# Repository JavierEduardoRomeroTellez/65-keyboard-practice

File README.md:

## 65-keyboard-practice
 Triying to make a 65% keyboard

#Images

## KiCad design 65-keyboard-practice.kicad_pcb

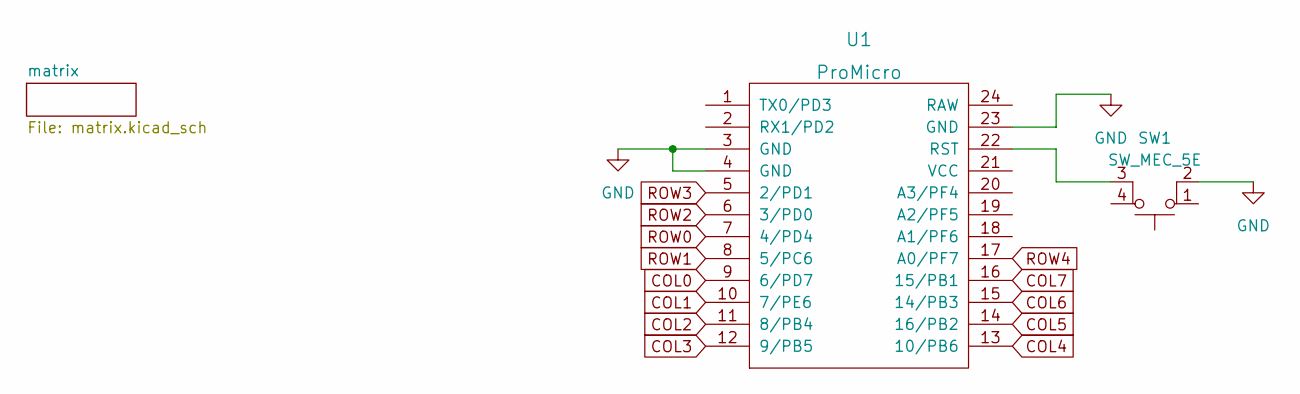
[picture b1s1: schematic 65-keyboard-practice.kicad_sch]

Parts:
SW1: SW_MEC_5E; PushButton_6x6mm_TH
U1: ProMicro; ArduinoProMicro

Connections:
COL0: U1.9 (6/PD7); also elsewhere on the board
COL1: U1.10 (7/PE6); also elsewhere on the board
COL2: U1.11 (8/PB4); also elsewhere on the board
COL3: U1.12 (9/PB5); also elsewhere on the board
COL4: U1.13 (10/PB6); also elsewhere on the board
COL5: U1.14 (16/PB2); also elsewhere on the board
COL6: U1.15 (14/PB3); also elsewhere on the board
COL7: U1.16 (15/PB1); also elsewhere on the board
GND: SW1.2, U1.3 (GND), U1.4 (GND), U1.23 (GND)
unnamed: SW1.3 (K), U1.22 (RST)
ROW0: U1.7 (4/PD4); also elsewhere on the board
ROW1: U1.8 (5/PC6); also elsewhere on the board
ROW2: U1.6 (3/PD0); also elsewhere on the board
ROW3: U1.5 (2/PD1); also elsewhere on the board
ROW4: U1.17 (A0/PF7); also elsewhere on the board

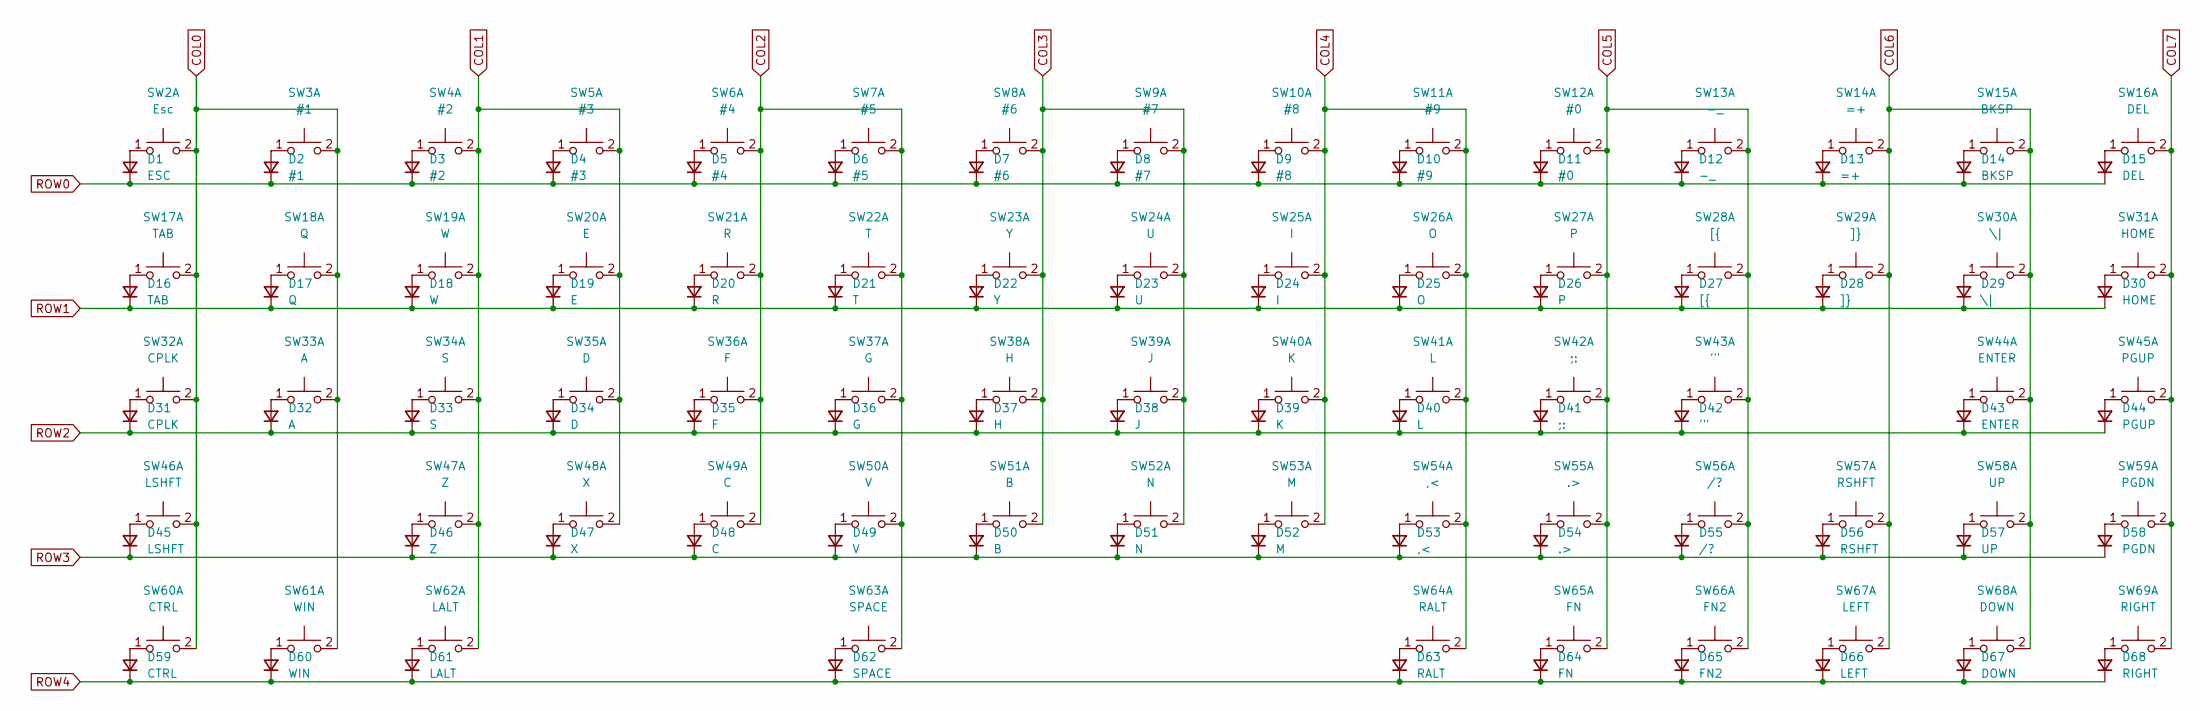
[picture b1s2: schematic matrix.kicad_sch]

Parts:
D1: ESC; D_DO-35_SOD27_P5.08mm_Horizontal
D2: #1; D_DO-35_SOD27_P5.08mm_Horizontal
D3: #2; D_DO-35_SOD27_P5.08mm_Horizontal
D4: #3; D_DO-35_SOD27_P5.08mm_Horizontal
D5: #4; D_DO-35_SOD27_P5.08mm_Horizontal
D6: #5; D_DO-35_SOD27_P5.08mm_Horizontal
D7: #6; D_DO-35_SOD27_P5.08mm_Horizontal
D8: #7; D_DO-35_SOD27_P5.08mm_Horizontal
D9: #8; D_DO-35_SOD27_P5.08mm_Horizontal
D10: #9; D_DO-35_SOD27_P5.08mm_Horizontal
D11: #0; D_DO-35_SOD27_P5.08mm_Horizontal
D12: -_; D_DO-35_SOD27_P5.08mm_Horizontal
D13: =+; D_DO-35_SOD27_P5.08mm_Horizontal
D14: BKSP; D_DO-35_SOD27_P5.08mm_Horizontal
D15: DEL; D_DO-35_SOD27_P5.08mm_Horizontal
D16: TAB; D_DO-35_SOD27_P5.08mm_Horizontal
D17: Q; D_DO-35_SOD27_P5.08mm_Horizontal
D18: W; D_DO-35_SOD27_P5.08mm_Horizontal
D19: E; D_DO-35_SOD27_P5.08mm_Horizontal
D20: R; D_DO-35_SOD27_P5.08mm_Horizontal
D21: T; D_DO-35_SOD27_P5.08mm_Horizontal
D22: Y; D_DO-35_SOD27_P5.08mm_Horizontal
D23: U; D_DO-35_SOD27_P5.08mm_Horizontal
D24: I; D_DO-35_SOD27_P5.08mm_Horizontal
D25: O; D_DO-35_SOD27_P5.08mm_Horizontal
D26: P; D_DO-35_SOD27_P5.08mm_Horizontal
D27: [{; D_DO-35_SOD27_P5.08mm_Horizontal
D28: ]}; D_DO-35_SOD27_P5.08mm_Horizontal
D29: \|; D_DO-35_SOD27_P5.08mm_Horizontal
D30: HOME; D_DO-35_SOD27_P5.08mm_Horizontal
D31: CPLK; D_DO-35_SOD27_P5.08mm_Horizontal
D32: A; D_DO-35_SOD27_P5.08mm_Horizontal
D33: S; D_DO-35_SOD27_P5.08mm_Horizontal
D34: D; D_DO-35_SOD27_P5.08mm_Horizontal
D35: F; D_DO-35_SOD27_P5.08mm_Horizontal
D36: G; D_DO-35_SOD27_P5.08mm_Horizontal
D37: H; D_DO-35_SOD27_P5.08mm_Horizontal
D38: J; D_DO-35_SOD27_P5.08mm_Horizontal
D39: K; D_DO-35_SOD27_P5.08mm_Horizontal
D40: L; D_DO-35_SOD27_P5.08mm_Horizontal
D41: ;:; D_DO-35_SOD27_P5.08mm_Horizontal
D42: '"; D_DO-35_SOD27_P5.08mm_Horizontal
D43: ENTER; D_DO-35_SOD27_P5.08mm_Horizontal
D44: PGUP; D_DO-35_SOD27_P5.08mm_Horizontal
D45: LSHFT; D_DO-35_SOD27_P5.08mm_Horizontal
D46: Z; D_DO-35_SOD27_P5.08mm_Horizontal
D47: X; D_DO-35_SOD27_P5.08mm_Horizontal
D48: C; D_DO-35_SOD27_P5.08mm_Horizontal
D49: V; D_DO-35_SOD27_P5.08mm_Horizontal
D50: B; D_DO-35_SOD27_P5.08mm_Horizontal
D51: N; D_DO-35_SOD27_P5.08mm_Horizontal
D52: M; D_DO-35_SOD27_P5.08mm_Horizontal
D53: ,<; D_DO-35_SOD27_P5.08mm_Horizontal
D54: .>; D_DO-35_SOD27_P5.08mm_Horizontal
D55: /?; D_DO-35_SOD27_P5.08mm_Horizontal
D56: RSHFT; D_DO-35_SOD27_P5.08mm_Horizontal
D57: UP; D_DO-35_SOD27_P5.08mm_Horizontal
D58: PGDN; D_DO-35_SOD27_P5.08mm_Horizontal
D59: CTRL; D_DO-35_SOD27_P5.08mm_Horizontal
D60: WIN; D_DO-35_SOD27_P5.08mm_Horizontal
D61: LALT; D_DO-35_SOD27_P5.08mm_Horizontal
D62: SPACE; D_DO-35_SOD27_P5.08mm_Horizontal
D63: RALT; D_DO-35_SOD27_P5.08mm_Horizontal
D64: FN; D_DO-35_SOD27_P5.08mm_Horizontal
D65: FN2; D_DO-35_SOD27_P5.08mm_Horizontal
D66: LEFT; D_DO-35_SOD27_P5.08mm_Horizontal
D67: DOWN; D_DO-35_SOD27_P5.08mm_Horizontal
D68: RIGHT; D_DO-35_SOD27_P5.08mm_Horizontal
SW2: Esc; MXOnly-1U-Hotswap
SW3: #1; MXOnly-1U-Hotswap
SW4: #2; MXOnly-1U-Hotswap
SW5: #3; MXOnly-1U-Hotswap
SW6: #4; MXOnly-1U-Hotswap
SW7: #5; MXOnly-1U-Hotswap
SW8: #6; MXOnly-1U-Hotswap
SW9: #7; MXOnly-1U-Hotswap
SW10: #8; MXOnly-1U-Hotswap
SW11: #9; MXOnly-1U-Hotswap
SW12: #0; MXOnly-1U-Hotswap
SW13: -_; MXOnly-1U-Hotswap
SW14: =+; MXOnly-1U-Hotswap
SW15: BKSP; MXOnly-2U-Hotswap
SW16: DEL; MXOnly-1U-Hotswap
SW17: TAB; MXOnly-1.5U-Hotswap
SW18: Q; MXOnly-1U-Hotswap
SW19: W; MXOnly-1U-Hotswap
SW20: E; MXOnly-1U-Hotswap
SW21: R; MXOnly-1U-Hotswap
SW22: T; MXOnly-1U-Hotswap
SW23: Y; MXOnly-1U-Hotswap
SW24: U; MXOnly-1U-Hotswap
SW25: I; MXOnly-1U-Hotswap
SW26: O; MXOnly-1U-Hotswap
SW27: P; MXOnly-1U-Hotswap
SW28: [{; MXOnly-1U-Hotswap
SW29: ]}; MXOnly-1U-Hotswap
SW30: \|; MXOnly-1.5U-Hotswap
SW31: HOME; MXOnly-1U-Hotswap
SW32: CPLK; MXOnly-1.75U-Hotswap
SW33: A; MXOnly-1U-Hotswap
SW34: S; MXOnly-1U-Hotswap
SW35: D; MXOnly-1U-Hotswap
SW36: F; MXOnly-1U-Hotswap
SW37: G; MXOnly-1U-Hotswap
SW38: H; MXOnly-1U-Hotswap
SW39: J; MXOnly-1U-Hotswap
SW40: K; MXOnly-1U-Hotswap
SW41: L; MXOnly-1U-Hotswap
SW42: ;:; MXOnly-1U-Hotswap
SW43: '"; MXOnly-1U-Hotswap
SW44: ENTER; MXOnly-2.25U-Hotswap
SW45: PGUP; MXOnly-1U-Hotswap
SW46: LSHFT; MXOnly-2.25U-Hotswap
SW47: Z; MXOnly-1U-Hotswap
SW48: X; MXOnly-1U-Hotswap
SW49: C; MXOnly-1U-Hotswap
SW50: V; MXOnly-1U-Hotswap
SW51: B; MXOnly-1U-Hotswap
SW52: N; MXOnly-1U-Hotswap
SW53: M; MXOnly-1U-Hotswap
SW54: ,<; MXOnly-1U-Hotswap
SW55: .>; MXOnly-1U-Hotswap
SW56: /?; MXOnly-1U-Hotswap
SW57: RSHFT; MXOnly-1.75U-Hotswap
SW58: UP; MXOnly-1U-Hotswap
SW59: PGDN; MXOnly-1U-Hotswap
SW60: CTRL; MXOnly-1.5U-Hotswap
SW61: WIN; MXOnly-1.25U-Hotswap
SW62: LALT; MXOnly-1.25U-Hotswap
SW63: SPACE; MXOnly-6U-Centered-Hotswap
SW64: RALT; MXOnly-1U-Hotswap
SW65: FN; MXOnly-1U-Hotswap
SW66: FN2; MXOnly-1U-Hotswap
SW67: LEFT; MXOnly-1U-Hotswap
SW68: DOWN; MXOnly-1U-Hotswap
SW69: RIGHT; MXOnly-1U-Hotswap

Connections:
COL0: SW2.2, SW3.2, SW17.2, SW18.2, SW32.2, SW33.2, SW46.2, SW60.2, SW61.2; also elsewhere on the board
COL1: SW4.2, SW5.2, SW19.2, SW20.2, SW34.2, SW35.2, SW47.2, SW48.2, SW62.2; also elsewhere on the board
COL2: SW6.2, SW7.2, SW21.2, SW22.2, SW36.2, SW37.2, SW49.2, SW50.2, SW63.2; also elsewhere on the board
COL3: SW8.2, SW9.2, SW23.2, SW24.2, SW38.2, SW39.2, SW51.2, SW52.2; also elsewhere on the board
COL4: SW10.2, SW11.2, SW25.2, SW26.2, SW40.2, SW41.2, SW53.2, SW54.2, SW64.2; also elsewhere on the board
COL5: SW12.2, SW13.2, SW27.2, SW28.2, SW42.2, SW43.2, SW55.2, SW56.2, SW65.2, SW66.2; also elsewhere on the board
COL6: SW14.2, SW15.2, SW29.2, SW30.2, SW44.2, SW57.2, SW58.2, SW67.2, SW68.2; also elsewhere on the board
COL7: SW16.2, SW31.2, SW45.2, SW59.2, SW69.2; also elsewhere on the board
unnamed: D1.2 (A), SW2.1
unnamed: D2.2 (A), SW3.1
unnamed: D3.2 (A), SW4.1
unnamed: D4.2 (A), SW5.1
unnamed: D5.2 (A), SW6.1
unnamed: D6.2 (A), SW7.1
unnamed: D7.2 (A), SW8.1
unnamed: D8.2 (A), SW9.1
unnamed: D9.2 (A), SW10.1
unnamed: D10.2 (A), SW11.1
unnamed: D11.2 (A), SW12.1
unnamed: D12.2 (A), SW13.1
unnamed: D13.2 (A), SW14.1
unnamed: D14.2 (A), SW15.1
unnamed: D15.2 (A), SW16.1
unnamed: D16.2 (A), SW17.1
unnamed: D17.2 (A), SW18.1
unnamed: D18.2 (A), SW19.1
unnamed: D19.2 (A), SW20.1
unnamed: D20.2 (A), SW21.1
unnamed: D21.2 (A), SW22.1
unnamed: D22.2 (A), SW23.1
unnamed: D23.2 (A), SW24.1
unnamed: D24.2 (A), SW25.1
unnamed: D25.2 (A), SW26.1
unnamed: D26.2 (A), SW27.1
unnamed: D27.2 (A), SW28.1
unnamed: D28.2 (A), SW29.1
unnamed: D29.2 (A), SW30.1
unnamed: D30.2 (A), SW31.1
unnamed: D31.2 (A), SW32.1
unnamed: D32.2 (A), SW33.1
unnamed: D33.2 (A), SW34.1
unnamed: D34.2 (A), SW35.1
unnamed: D35.2 (A), SW36.1
unnamed: D36.2 (A), SW37.1
unnamed: D37.2 (A), SW38.1
unnamed: D38.2 (A), SW39.1
unnamed: D39.2 (A), SW40.1
unnamed: D40.2 (A), SW41.1
unnamed: D41.2 (A), SW42.1
unnamed: D42.2 (A), SW43.1
unnamed: D43.2 (A), SW44.1
unnamed: D44.2 (A), SW45.1
unnamed: D45.2 (A), SW46.1
unnamed: D46.2 (A), SW47.1
unnamed: D47.2 (A), SW48.1
unnamed: D48.2 (A), SW49.1
unnamed: D49.2 (A), SW50.1
unnamed: D50.2 (A), SW51.1
unnamed: D51.2 (A), SW52.1
unnamed: D52.2 (A), SW53.1
unnamed: D53.2 (A), SW54.1
unnamed: D54.2 (A), SW55.1
unnamed: D55.2 (A), SW56.1
unnamed: D56.2 (A), SW57.1
unnamed: D57.2 (A), SW58.1
unnamed: D58.2 (A), SW59.1
unnamed: D59.2 (A), SW60.1
unnamed: D60.2 (A), SW61.1
unnamed: D61.2 (A), SW62.1
unnamed: D62.2 (A), SW63.1
unnamed: D63.2 (A), SW64.1
unnamed: D64.2 (A), SW65.1
unnamed: D65.2 (A), SW66.1
unnamed: D66.2 (A), SW67.1
unnamed: D67.2 (A), SW68.1
unnamed: D68.2 (A), SW69.1
ROW0: D1.1 (K), D2.1 (K), D3.1 (K), D4.1 (K), D5.1 (K), D6.1 (K), D7.1 (K), D8.1 (K), D9.1 (K), D10.1 (K), D11.1 (K), D12.1 (K), D13.1 (K), D14.1 (K), D15.1 (K); also elsewhere on the board
ROW1: D16.1 (K), D17.1 (K), D18.1 (K), D19.1 (K), D20.1 (K), D21.1 (K), D22.1 (K), D23.1 (K), D24.1 (K), D25.1 (K), D26.1 (K), D27.1 (K), D28.1 (K), D29.1 (K), D30.1 (K); also elsewhere on the board
ROW2: D31.1 (K), D32.1 (K), D33.1 (K), D34.1 (K), D35.1 (K), D36.1 (K), D37.1 (K), D38.1 (K), D39.1 (K), D40.1 (K), D41.1 (K), D42.1 (K), D43.1 (K), D44.1 (K); also elsewhere on the board
ROW3: D45.1 (K), D46.1 (K), D47.1 (K), D48.1 (K), D49.1 (K), D50.1 (K), D51.1 (K), D52.1 (K), D53.1 (K), D54.1 (K), D55.1 (K), D56.1 (K), D57.1 (K), D58.1 (K); also elsewhere on the board
ROW4: D59.1 (K), D60.1 (K), D61.1 (K), D62.1 (K), D63.1 (K), D64.1 (K), D65.1 (K), D66.1 (K), D67.1 (K), D68.1 (K); also elsewhere on the board

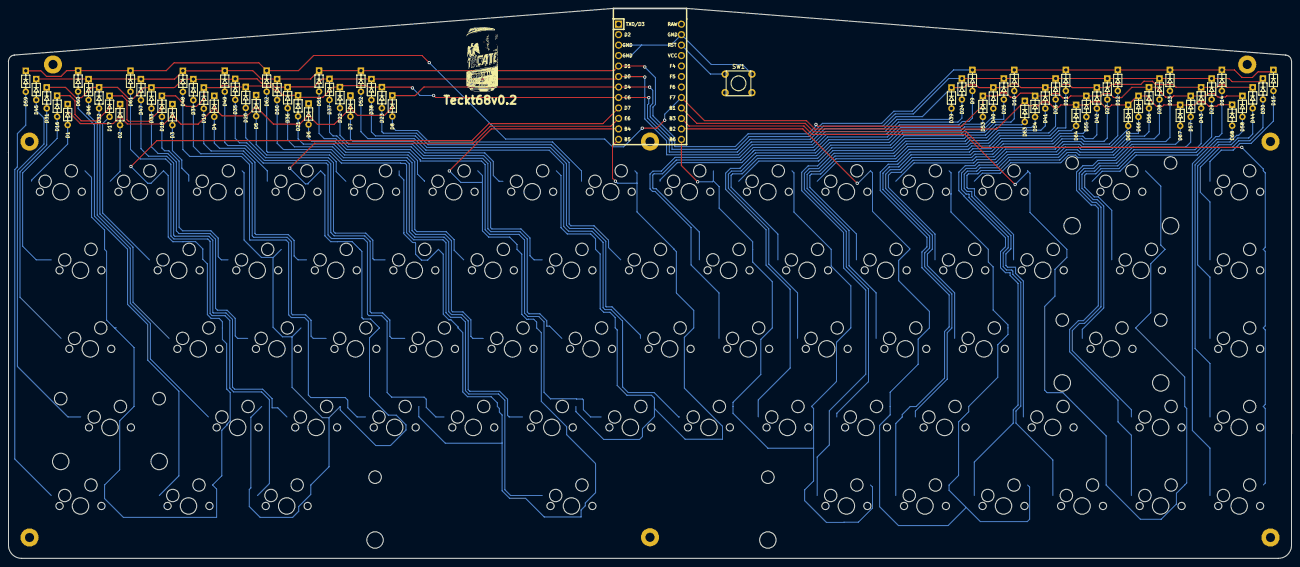
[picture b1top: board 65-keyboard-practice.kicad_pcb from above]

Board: 2 copper layers, 311.2 x 133.4 mm, 139 parts (0 on the bottom side), 83 nets.

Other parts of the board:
.: LOGO

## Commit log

2022-05-14 submodules submodules submodules
2022-05-19 Base project created
2022-05-19 Added submodule
2022-05-19 same submodule
2022-05-19 Imported libraries
2022-05-19 Matrix created
2022-05-19 added GND and reset button to the promicro
2022-05-19 added some submodules
2022-05-21 half wiring done
2022-05-21 Finished the design
2022-06-28 Limpieza de routing y remplazo de footprints
2022-06-28 Finished provisional routing
2022-06-29 Some esthetic details
2022-06-29 Added mounting holes
2022-06-29 Added rgb underglow
2022-06-29 Change the name
